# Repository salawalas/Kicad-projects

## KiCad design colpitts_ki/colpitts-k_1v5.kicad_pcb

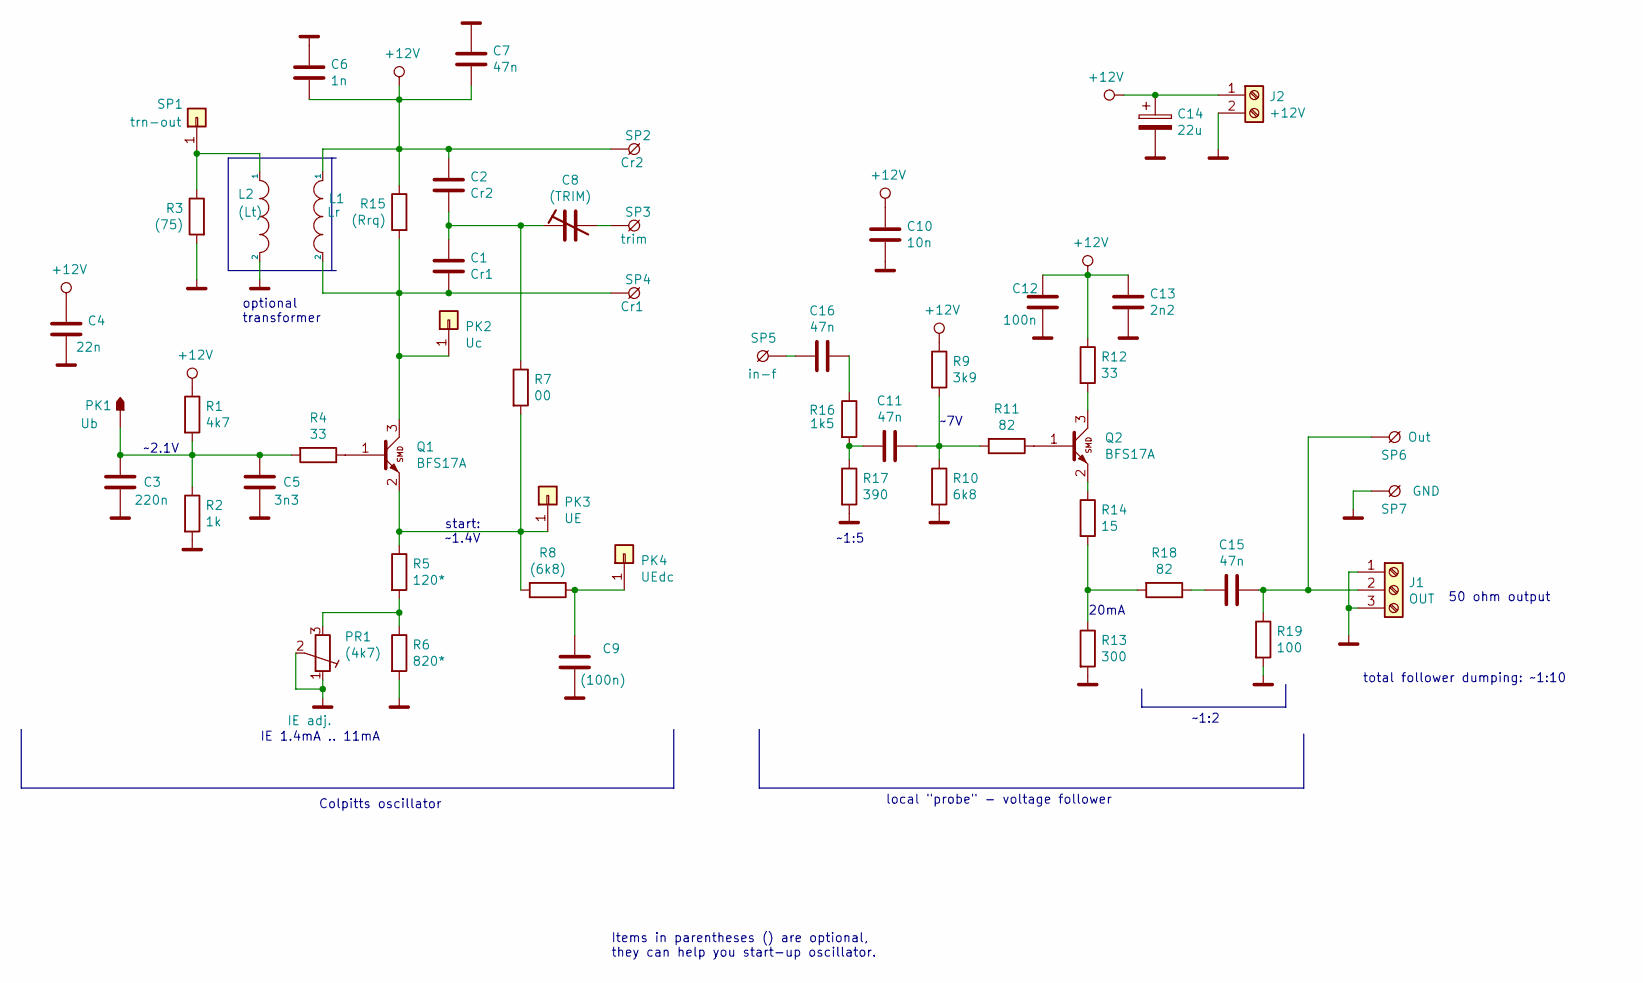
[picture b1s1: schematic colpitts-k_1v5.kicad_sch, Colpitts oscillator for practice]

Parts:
C1: Cr1; R_0805_AB
C2: Cr2; R_0805_AB
C3: 220n; R_0805_AB
C4: 22n; R_0805_AB
C5: 3n3; R_0805_AB
C6: 1n; R_0805_AB
C7, C11, C15, C16: 47n; R_0805_AB
C8: (TRIM); C_Trimmer_Murata_TZB4-A
C9: (100n); R_0805_AB
C10: 10n; R_0805_AB
C12: 100n; R_0805_AB
C13: 2n2; R_0805_AB
C14: 22u; CPEm
J1: OUT; ak550_3
J2: +12V; ak550_2
L1: Lr; CN
L2: (Lt); CN
PK1: Ub; ts65
PK2: Uc; Pin_Header_Straight_1x01_Pitch2.54mm
PK3: UE; Pin_Header_Straight_1x01_Pitch2.54mm
PK4: UEdc; Pin_Header_Straight_1x01_Pitch2.54mm
PR1: (4k7); PR
Q1, Q2: BFS17A; SOT-23
R1: 4k7; R_0805_AB
R2: 1k; R_0805_AB
R3: (75); R_0805_AB
R4, R12: 33; R_0805_AB
R5: 120*; R_0805_AB
R6: 820*; R_0805_AB
R7: 00; R_1206_AB
R8: (6k8); R_0805_AB
R9: 3k9; R_0805_AB
R10: 6k8; R_0805_AB
R11, R18: 82; R_0805_AB
R13: 300; R_0805_AB
R14: 15; R_0805_AB
R15: (Rrq); R_0805_AB
R16: 1k5; R_0805_AB
R17: 390; R_0805_AB
R19: 100; R_0805_AB
SP1: trn-out; Pin_Header_Straight_1x01_Pitch2.54mm
SP2: Cr2; ts70
SP3: trim; ts70
SP4: Cr1; ts70
SP5: in-f; ts70x120
SP6: Out; ts70x120
SP7: GND; ts70x120

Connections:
+12V: C2.1, C4.1, C6.2, C7.2, C10.1, C12.1, C13.1, C14.1, J2.1, L1.1, R1.1, R9.1, R12.1, R15.1, SP2.1
GND: C3.2, C4.2, C5.2, C6.1, C7.1, C9.2, C10.2, C12.2, C13.2, C14.2, J1.1, J1.3, J2.2, L2.2, PR1.1, PR1.2, R2.2, R3.2, R6.2, R10.2, R13.2, R17.2, R19.2, SP7.1
unnamed: C1.1, C2.2, C8.1, R7.1
unnamed: C1.2, L1.2, PK2.1, Q1.3 (C), R15.2, SP4.1
unnamed: C3.1, C5.1, PK1.1, R1.2, R2.1, R4.2
unnamed: C8.2, SP3.1
unnamed: C9.1, PK4.1, R8.1
unnamed: C11.1, R9.2, R10.1, R11.2
unnamed: C11.2, R16.2, R17.1
unnamed: C15.1, J1.2, R19.1, SP6.1
unnamed: C15.2, R18.1
unnamed: C16.1, R16.1
unnamed: C16.2, SP5.1
unnamed: L2.1, R3.1, SP1.1
unnamed: PK3.1, Q1.2 (E), R5.1, R7.2, R8.2
unnamed: PR1.3, R5.2, R6.1
unnamed: Q1.1 (B), R4.1
unnamed: Q2.1 (B), R11.1
unnamed: Q2.2 (E), R14.1
unnamed: Q2.3 (C), R12.2
unnamed: R13.1, R14.2, R18.2

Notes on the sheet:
~7V
local "probe" - voltage follower
~1:5
~1:2
total follower dumping: ~1:10
50 ohm output
Items in parentheses () are optional, they can help you start-up oscillator.
optional transformer
start: ~1.4V
Colpitts oscillator
20mA
IE 1.4mA .. 11mA
~2.1V

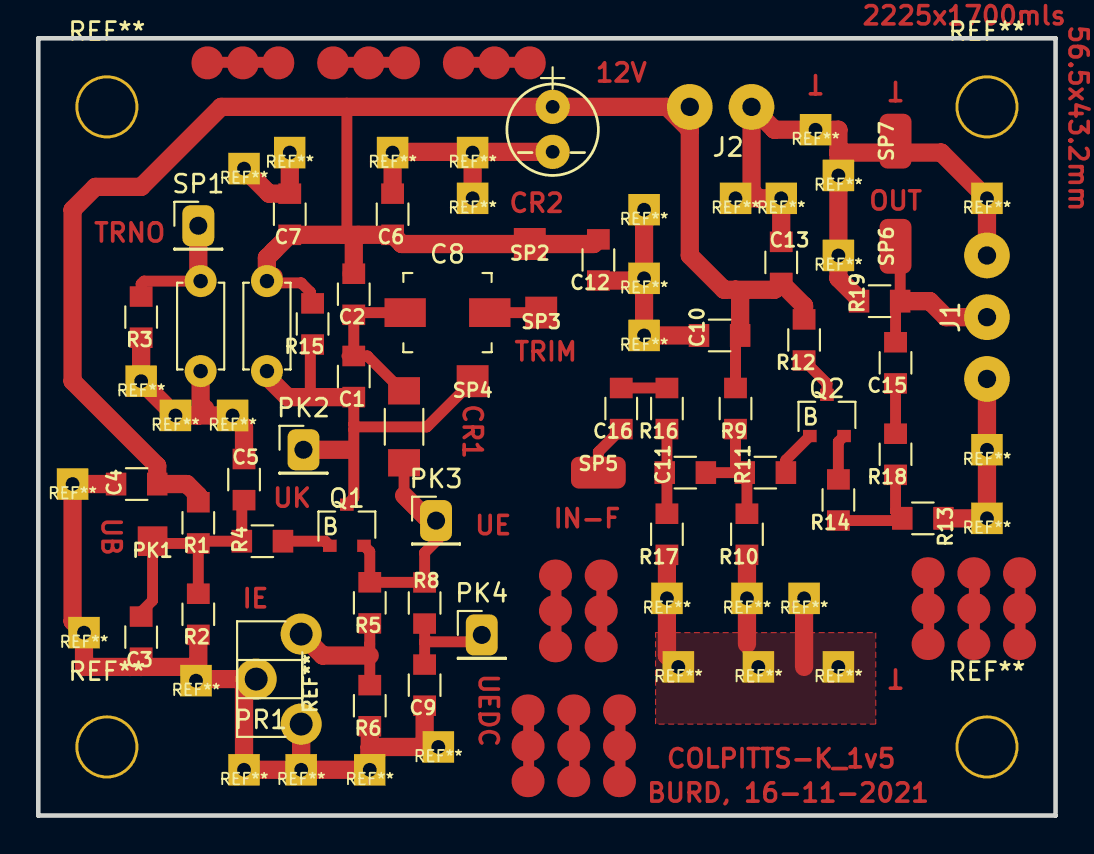
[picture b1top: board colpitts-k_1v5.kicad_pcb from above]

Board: 2 copper layers, 56.5 x 43.2 mm, 53 parts (0 on the bottom side), 21 nets.

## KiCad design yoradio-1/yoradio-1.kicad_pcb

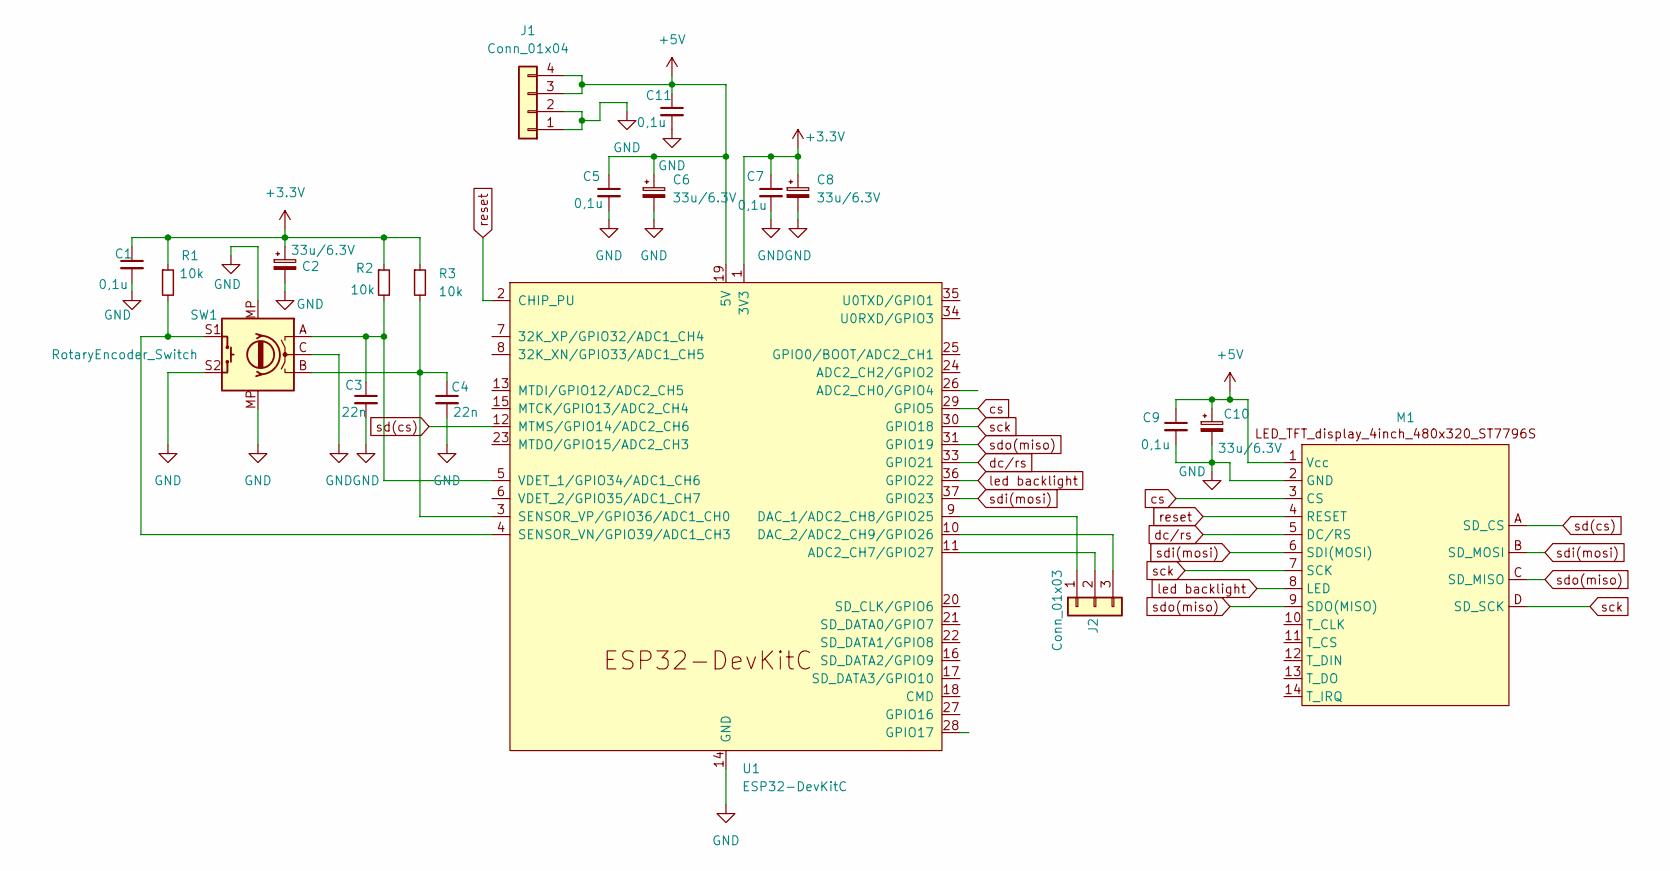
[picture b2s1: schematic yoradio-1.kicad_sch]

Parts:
C1, C5, C7, C9, C11: 0,1u; C_1206_3216Metric_Pad1.33x1.80mm_HandSolder
C2, C6, C8, C10: 33u/6.3V; CP_Radial_Tantal_D7.0mm_P5.00mm
C3, C4: 22n; C_1206_3216Metric_Pad1.33x1.80mm_HandSolder
J1: Conn_01x04; Molex_KK-254_AE-6410-04A_1x04_P2.54mm_Vertical
J2: Conn_01x03; JST_PH_B3B-PH-K_1x03_P2.00mm_Vertical
M1: TFT_displayLED_TFT_display_4inch_480x320_ST7796S
R1, R2, R3: 10k; R_1206_3216Metric_Pad1.30x1.75mm_HandSolder
SW1: RotaryEncoder_Switch; RotaryEncoder_Alps_EC11E-Switch_Vertical_H20mm
U1: ESP32-DevKitC; ESP32-DevKitC_ver2

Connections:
+3.3V: C1.1, C2.1, C7.1, C8.1, R1.1, R2.1, R3.1, U1.1 (3V3)
+5V: C5.1, C6.1, C9.1, C10.1, C11.1, J1.3, J1.4, M1.1 (Vcc), U1.19 (5V)
GND: C1.2, C2.2, C3.2, C4.2, C5.2, C6.2, C7.2, C8.2, C9.2, C10.2, C11.2, J1.1, J1.2, M1.2 (GND), SW1.C, SW1.MP, SW1.S2, U1.14 (GND), U1.32 (GND), U1.38 (GND)
unnamed: J2.1, U1.9 (DAC_1/ADC2_CH8/GPIO25)
unnamed: J2.2, U1.11 (ADC2_CH7/GPIO27)
unnamed: J2.3, U1.10 (DAC_2/ADC2_CH9/GPIO26)
unnamed: R1.2, SW1.S1, U1.4 (SENSOR_VN/GPIO39/ADC1_CH3)
unnamed: C4.1, R3.2, SW1.B, U1.3 (SENSOR_VP/GPIO36/ADC1_CH0)
unnamed: C3.1, R2.2, SW1.A, U1.5 (VDET_1/GPIO34/ADC1_CH6)
cs: M1.3 (CS), U1.29 (GPIO5)
dc/rs: M1.5 (DC/RS), U1.33 (GPIO21)
led backlight: M1.8 (LED), U1.36 (GPIO22)
reset: M1.4 (RESET), U1.2 (CHIP_PU)
sck: M1.7 (SCK), M1.D (SD_SCK), U1.30 (GPIO18)
sd(cs): M1.A (SD_CS), U1.12 (MTMS/GPIO14/ADC2_CH6)
sdi(mosi): M1.6 (SDI(MOSI)), M1.B (SD_MOSI), U1.37 (GPIO23)
sdo(miso): M1.9 (SDO(MISO)), M1.C (SD_MISO), U1.31 (GPIO19)

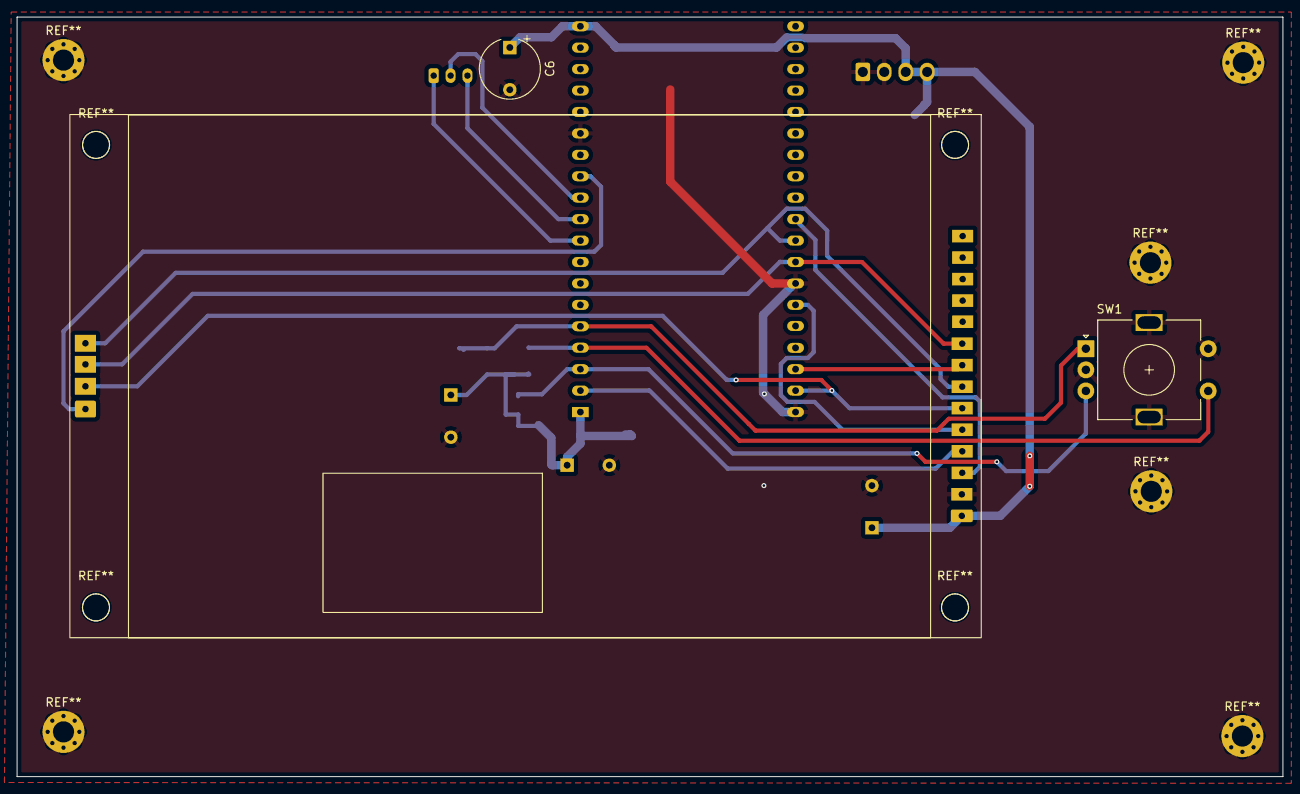
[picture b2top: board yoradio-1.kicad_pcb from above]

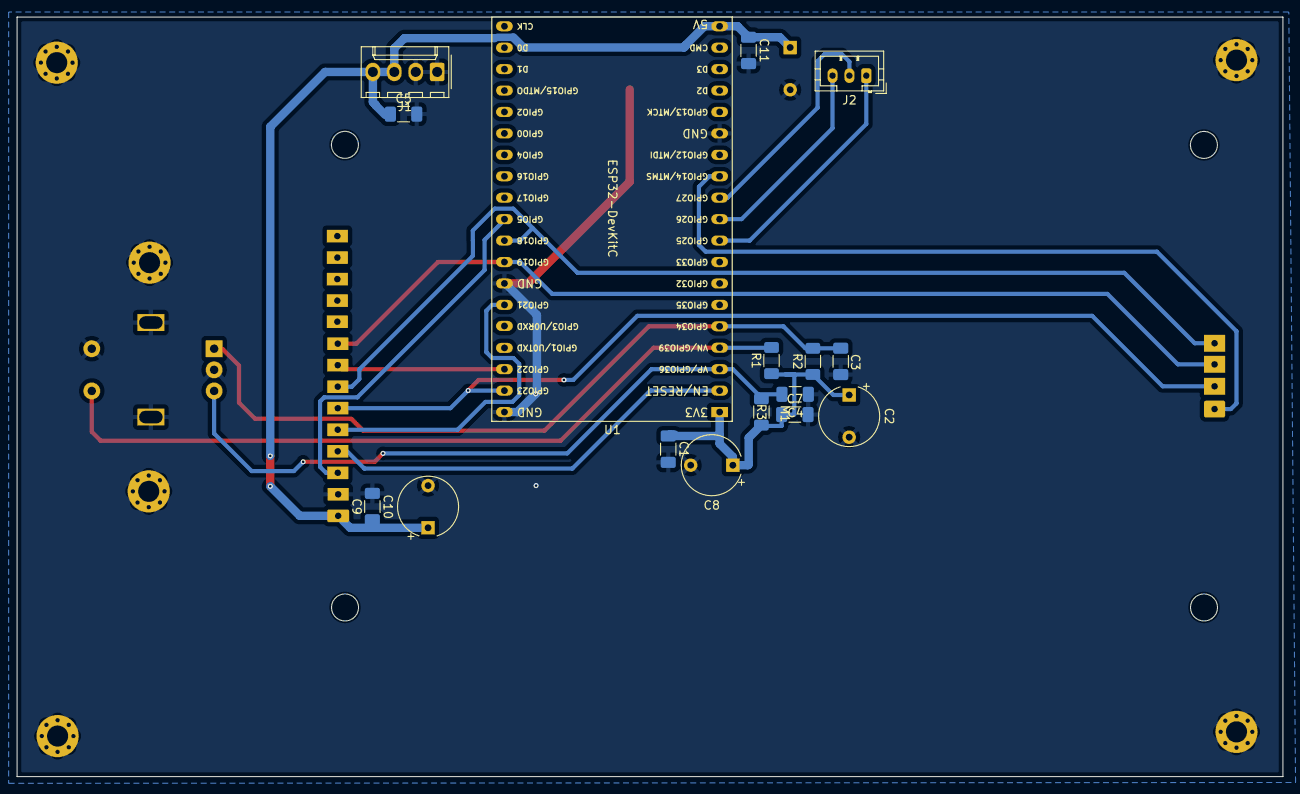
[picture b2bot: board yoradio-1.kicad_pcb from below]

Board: 2 copper layers, 150.0 x 90.0 mm, 19 parts (16 on the bottom side), 17 nets.
